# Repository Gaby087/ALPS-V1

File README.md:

```
                    *                    
                   ***                  
                  *****                 
                 *******                
                ** *** **               
               **   *   **        *     
              **         **      ***    
             **           **    *****   
            **             **  ** * **  
           **               ****   ****  
          **_________________**______**_ 
        ═══════════════════════════════════
                  A  L  P  S              
          Adjustable Lab Power Supply     
        ═══════════════════════════════════
```

# Adjustable Lab Power Supply - 12V 1A

## Approach and Objective of the Project

This is a simple design for a 12V 1A power supply, used more as a project to learn how to use KiCad, learn PCB design rules and make full documentation of every choice and all the theoretical values and calculations for this specific design. I decided to make this project just because it was the first circuit I ever made when I got into electronics in school. For the calculations I use 5 decimals just to make it more "precise". In this project I use 12V because I thought it's the minimum recommended for testing electronics and you can find cheaper transformers for this voltage. This also comes with some complications for the design and calculations in the "Worst Case Scenario". My personal recommendation is to get a 24V transformer for more margin in border situations, like when you connect a load that consumes the full 1A from the power supply.

The whole idea behind the documentation is something I always felt was missing when I was learning. A lot of projects just say "12V 1A power supply" and show you a schematic, but they never explain how they got there, if those 12V at 1A are real, or how much ripple that DC signal actually has. So here I try to write down every calculation and every decision, even the ones that show the limitations of the design. I find it genuinely useful when documentation goes beyond the final result, so I try to write my own projects that way.

## Schematic Design and Calculations

In this circuit I start by calculating the theoretical maximum voltage after the rectifying phase for this specific transformer (12Vrms). The maximum voltage, or peak voltage, should be:

```math
12 \cdot\sqrt{2}=16.97056[V]
```

We must consider that we are using a full bridge rectifier, so in each cycle of the sinusoidal wave the alternating current passes through 2 diodes. I will use the worst case scenario from the 1N4007 NXP Semiconductors datasheet, where the forward voltage is 1.1V at 25°C. Due to the fabrication process, diodes have a negative temperature coefficient, so at higher temperatures this voltage will be lower. Assuming the 25°C situation, we are losing 2.2V in the rectifying phase, so the remaining voltage is:

```math
16.97056-2.2=14.77056[V]
```

For the capacitor calculation I will use the formula:

```math
V_{rr}=\frac{I}{2fC}
```

Since this is a full bridge rectifier, the frequency doubles — that is the reason I use `2f` instead of just `f`. I will use a 4700μF capacitor. The reason behind this choice is that it is the most common high-capacitance commercial value. In future versions I will leave space for 2 extra optional capacitors, just in case you are crazy enough (like me) to want the system to be as stable and precise as possible. Using 1A as `I`, 50Hz as `f`, and 4700μF as `C`, we obtain a beautiful and horrific ripple voltage of 2.12765Vr, which leaves us with:

```math
14.77056-2.12765=12.64291[V]
```

This is the main reason why I recommend using a 24V transformer instead of 12V — this phase consumes a large portion of the original AC voltage to convert it to DC. So far we have a 12.6Vdc supply, but in order to make it adjustable we need to use an LDO like the LM317. If we read the LM317 datasheet we notice that the required headroom voltage is 3V, meaning we need at least 15V at the input for a 12V output. As we can see, we do not fulfill that condition. We are close enough to call this a 12V regulator, though in the worst case you could also say that I lied to you in the title — and that would also be true. I probably should have called this a 9V 1A regulator, but 12V 1A sounds better and sells more. To be serious though: in practice, at partial load the ripple voltage decreases, meaning the input to the LM317 stays above the required headroom. Full 1A load represents the worst case scenario described above.

## Output Voltage Adjustment

Now that we have our DC voltage we need to make it adjustable, and that is where the LM317 does its job. Internally the LM317 always keeps a reference voltage of 1.25V between its output pin (VO) and the adjustment pin (ADJ). Using that reference and a resistor divider we can set the output voltage with this formula:

```math
V_{out}=1.25\cdot\left(1+\frac{R2}{R1}\right)+I_{adj}\cdot R2
```

The `Iadj` current is around 50μA, so small that almost everyone ignores it in practice, which leaves us with the simplified formula:

```math
V_{out}=1.25\cdot\left(1+\frac{R2}{R1}\right)
```

In my circuit R1 is a fixed 240Ω resistor between VO and ADJ, and R2 is the combination of two potentiometers in series between ADJ and GND, one for coarse adjustment and one for fine adjustment. The minimum output voltage happens when R2 is 0Ω:

```math
V_{out}=1.25\cdot\left(1+\frac{0}{240}\right)=1.25000[V]
```

For the maximum I provide two resistor configurations depending on the transformer you want to use:

**For a 12V transformer (practical range 1.25V - 9V):**
- RV1 = 1K (fine adjust)
- RV2 = 2K (coarse adjust)
- Total R2 = 3000Ω

```math
V_{out}=1.25\cdot\left(1+\frac{3000}{240}\right)=16.87500[V]
```

**For a 24V transformer (practical range 1.25V - 20V) — used in this schematic:**
- RV1 = 1K (fine adjust)
- RV2 = 5K (coarse adjust)
- Total R2 = 6000Ω

```math
V_{out}=1.25\cdot\left(1+\frac{6000}{240}\right)=32.50000[V]
```

In both cases the theoretical maximum is way above what we can actually reach, because the real limit is always set by the input voltage, not by the resistors. The regulator does not do magic, if you only have 12.6V at the input you are not getting 32V at the output no matter what the formula says. I used the 5K configuration in the schematic so the board is ready for a 24V transformer in future versions, but if you are building this with a 12V transformer the 2K version gives you a finer and more useful adjustment over the range you can actually use.

## Power Dissipation and Thermal Considerations

This is the part most people skip and then wonder why their LM317 shuts down or burns their finger. The LM317 is a linear regulator, which means it dissipates the voltage difference between input and output as heat. The power it has to dissipate is:

```math
P_{diss}=(V_{in}-V_{out})\cdot I
```

The worst case here is not at maximum voltage, it is at minimum output voltage with maximum current, because that is when the voltage difference is the largest. If someone sets the output to the minimum 1.25V while pulling the full 1A from a 12.6V input:

```math
P_{diss}=(12.64291-1.25)\cdot 1=11.39291[W]
```

That is a lot of heat for a small TO-220 package, basically you just built a 11W heater that also happens to regulate voltage. The LM317 in a TO-220 package without a heatsink has a thermal resistance from junction to ambient of around 50°C/W, so even at a more reasonable 3.6W (output at 9V, 1A) the junction temperature rise would be:

```math
\Delta T=3.6\cdot 50=180[°C]
```

The LM317 has internal thermal protection that shuts it down around 125-150°C, so it will not destroy itself, it will just turn off and ruin your day. The conclusion is simple: **you must use a heatsink** if you plan to use this supply at high currents or large voltage differences. With a decent heatsink the thermal resistance drops to around 5°C/W, which keeps everything under control:

```math
\Delta T=3.6\cdot 5=18[°C]
```

This is one more reason why I keep saying that a 24V transformer is a better idea only if you also size the heatsink properly, because more input voltage also means more heat to dissipate when the output is low.

## Output Stage

After the regulator I use a 10μF capacitor (C2) at the output. The LM317 datasheet recommends an output capacitor to improve transient response and stability, and 10μF is a safe and common value for this. I also keep a 0.1μF ceramic capacitor (C3) at the input of the regulator right next to it as a bypass capacitor, because the big 4700μF electrolytic is slow at high frequencies and a small ceramic covers the high frequency noise that the electrolytic cannot handle well. Mixing a big electrolytic for bulk capacitance and a small ceramic for bypass is standard practice and costs almost nothing.

## Bill of Materials (BOM)

| Reference | Component | Value | Notes |
|-----------|-----------|-------|-------|
| J1 | Screw terminal KF301-2P | - | AC input from transformer |
| J2 | Screw terminal KF301-2P | - | DC output |
| D1-D4 | Diode 1N4007 | - | Full bridge rectifier |
| C1 | Electrolytic capacitor | 4700μF | Bulk filtering |
| C3 | Ceramic capacitor | 0.1μF | Input bypass |
| C2 | Electrolytic capacitor | 10μF | Output stability |
| U1 | LDO regulator LM317 | TO-220 | Heatsink recommended |
| R1 | Resistor | 240Ω | Fixed divider resistor |
| RV1 | Potentiometer | 1K | Fine adjust |
| RV2 | Potentiometer | 5K (or 2K) | Coarse adjust |

## Images

### Schematic

### PCB Layout

### 3D Render

## Notes and Honesty Section

Just to be completely clear about what this project is and what it is not:

- The "12V 1A" in the title is the nominal target, not a guarantee at every operating point. As explained above, the real output range depends on your transformer, and with a 12V transformer the practical maximum is closer to 9V at full load.
- A heatsink is not optional if you push this supply hard. The bare TO-220 will overheat and shut down.
- This is a learning project, not a replacement for a commercial bench supply. It will not compete with a proper lab supply, but it is a great way to understand every stage of a linear regulated power supply from the ground up.

If this documentation or the design is useful for someone learning the same things I am learning, feel free to use anything here.

---

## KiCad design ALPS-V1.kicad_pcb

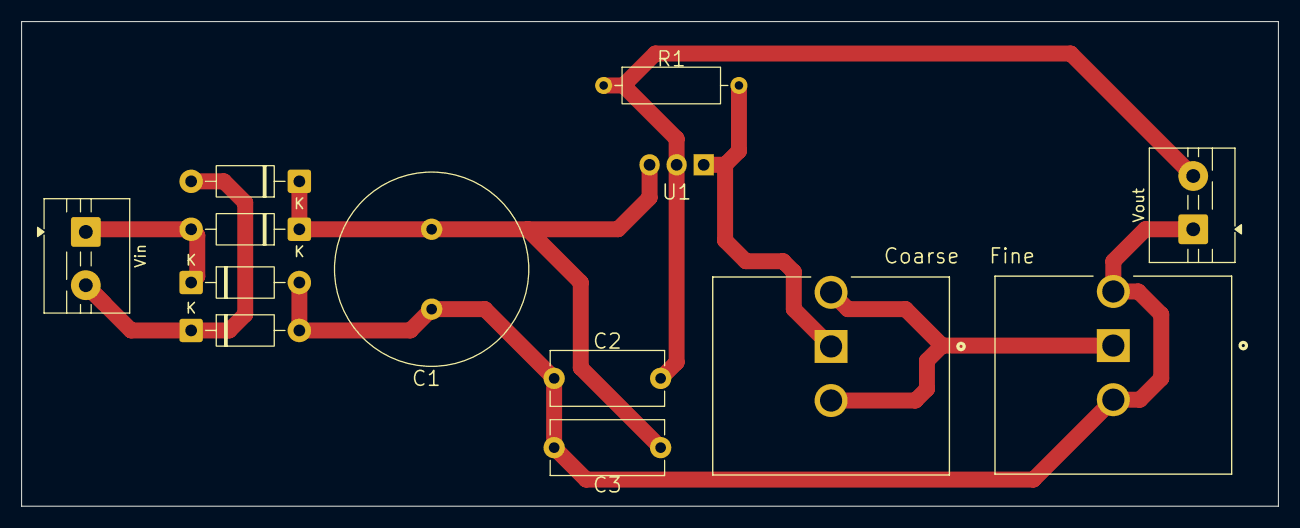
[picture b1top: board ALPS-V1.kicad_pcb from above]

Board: 2 copper layers, 118.0 x 45.5 mm, 13 parts (1 on the bottom side), 7 nets.

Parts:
C1: 4700uF; C_Radial_D18.0mm_H35.5mm_P7.50mm
C2: 10uF; C_Disc_D10.5mm_W5.0mm_P10.00mm
C3: 0.1uF; C_Disc_D10.5mm_W5.0mm_P10.00mm
Coarse: 5K; TRIM_3590S-2-103L
D1, D2, D3, D4: 1N4007; D_DO-41_SOD81_P10.16mm_Horizontal
Fine: 1K; TRIM_3590S-2-103L
R1: 240; R_Axial_DIN0309_L9.0mm_D3.2mm_P12.70mm_Horizontal
U1: LM317_TO-220; TO-220-3_Vertical
Vin: KF301-2P; TerminalBlock_MaiXu_MX126-5.0-02P_1x02_P5.00mm
Vout: KF301-2P; TerminalBlock_MaiXu_MX126-5.0-02P_1x02_P5.00mm

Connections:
GND: C1.2, C2.2, C3.2, D1.2 (A), D2.2 (A), Fine.2, Fine.3, Vout.1
unnamed: D1.1 (K), D3.2 (A), Vin.1
unnamed: D2.1 (K), D4.2 (A), Vin.2
unnamed: C1.1, C3.1, D3.1 (K), D4.1 (K), U1.3 (VI)
unnamed: Coarse.2, Coarse.3, Fine.1
unnamed: Coarse.1, R1.2, U1.1 (ADJ)
unnamed: C2.1, R1.1, U1.2 (VO), Vout.2

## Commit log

2026-05-27 Initial commit - V1 KiCad files
2026-05-27 Add README with calculations and design documentation
2026-05-27 Rename project files from SimpleVoltageRegulator to ALPS-V1
2026-05-27 New ascii art
    add a ascii art to make the document looks better
2026-05-27 Remove decorative line from README
2026-05-28 Add README and images
2026-05-28 Add schematic and 3D render images
2026-05-28 Readme calculations(still wip)
2026-05-28 Corrected README format
2026-05-28 Changed the label for the 5k potentiometer
2026-05-28 README finished
2026-05-28 Fix image filename for PCB Layout in README
2026-05-30 Render Images
2026-05-30 Replace 3D render images with new versions
    Updated 3D render images in the README.
